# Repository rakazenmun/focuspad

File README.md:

# Focuspad

Focuspad is a six-key productivity macropad built around the Seeed Studio XIAO
RP2040. It combines a 2×3 diode matrix, a pressable rotary encoder, and a
128×32 OLED in a compact 3D-printed enclosure.

I wanted a small desktop controller that keeps the shortcuts I use most within
one hand. The default KMK layout provides Copy, Paste, Undo, Reopen Closed Tab,
Find, and Enter. Turning the encoder changes volume; pressing it mutes.

## PCB

The two-layer PCB is 97×68 mm. Six 1N4148 diodes prevent ghosting in the 2×3
matrix. The OLED uses D4/D5 for I²C, and the encoder uses D7–D9. All footprints
are embedded in the KiCad board file.

KiCad 10 error-level DRC result: **0 violations and 0 unconnected pads**.
KiCad 10 error-level ERC result: **0 violations**. Reports are included in the
`PCB` directory. The design has not yet been manufactured or hardware-tested.

## Case

The case is a two-part PLA print with a 1.5 mm MX switch plate, four M3 heat-set
bosses, a USB-C opening, and 0.25 mm clearance around the PCB. The complete
assembly is in `CAD/Focuspad_Assembly.step`; printable STEP and STL parts are in
`production/`.

## Firmware

`Firmware/main.py` is original KMK firmware for CircuitPython. Installation and
library requirements are documented in `Firmware/README.md`. A production copy
is available at `production/main.py`.

## Repository structure

- `CAD/` — complete STEP assembly
- `PCB/` — KiCad project, schematic, PCB, DRC, and ERC reports
- `Firmware/` — KMK source and installation notes
- `production/` — Gerbers, printable case parts, and firmware
- `assets/` — README renders
- `BOM.csv` — bill of materials with links

## Bill of materials

| Qty | Part |
|---:|---|
| 1 | Seeed Studio XIAO RP2040 |
| 6 | MX-compatible switches |
| 6 | 1U keycaps |
| 6 | 1N4148 DO-35 diodes |
| 1 | EC11 rotary encoder with push switch |
| 1 | 0.91-inch 128×32 SSD1306 OLED |
| 4 | M3×16 socket-head screws |
| 4 | M3×5×4 heat-set inserts |
| 1 | Two-layer PCB |
| 1 | Two-part PLA case |

See `BOM.csv` for source links and notes.

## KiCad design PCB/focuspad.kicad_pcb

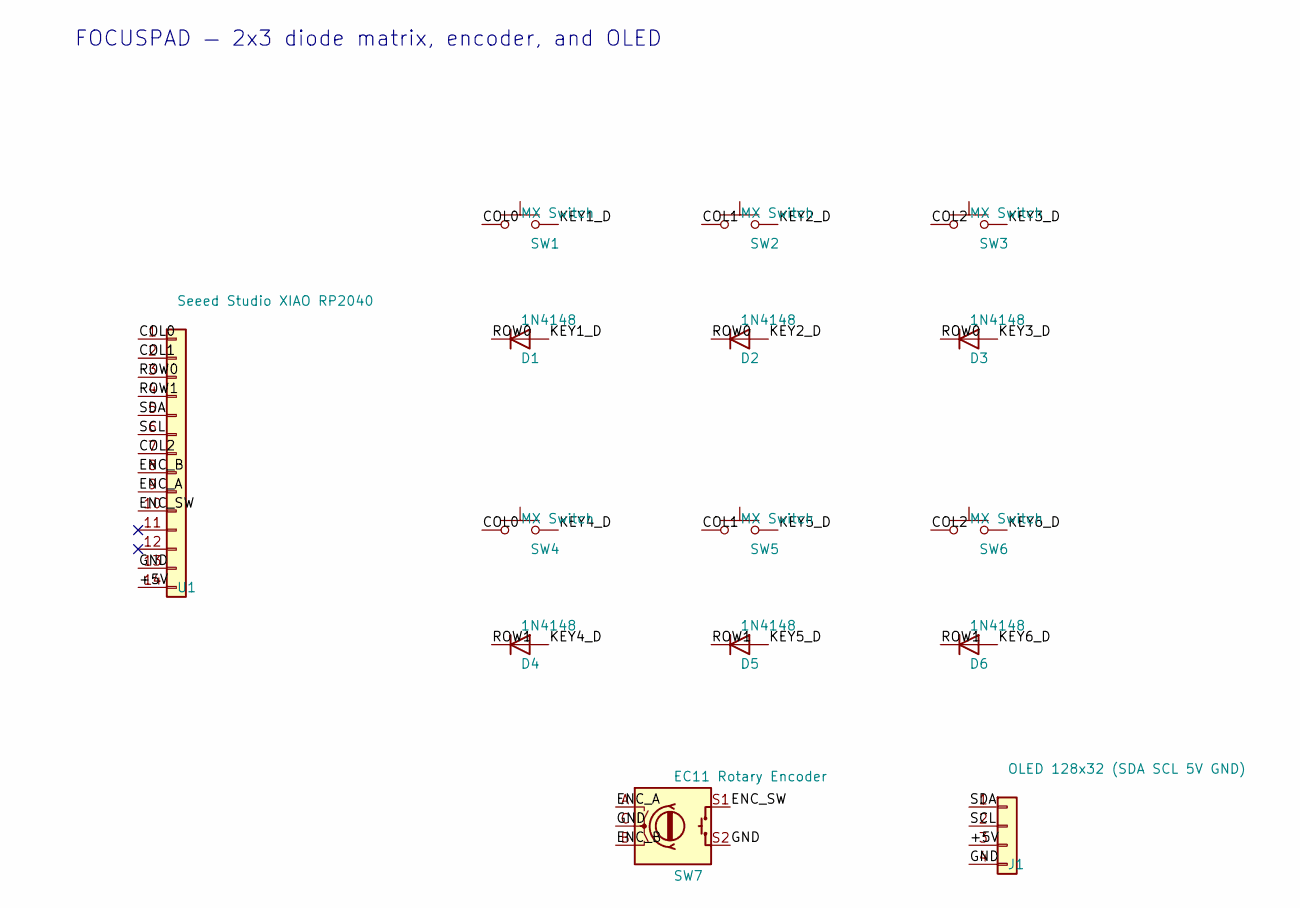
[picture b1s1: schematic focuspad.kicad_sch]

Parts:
D1, D2, D3, D4, D5, D6: 1N4148; D_DO-35_SOD27_P7.62mm_Horizontal
J1: OLED 128x32 (SDA SCL 5V GND); PinHeader_1x04_P2.54mm_Vertical
SW1, SW2, SW3, SW4, SW5, SW6: MX Switch; MX-Solderable-1U
SW7: EC11 Rotary Encoder; RotaryEncoder_Alps_EC11E-Switch_Vertical_H20mm
U1: Seeed Studio XIAO RP2040; XIAO-Generic-Hybrid-14P-2.54-21X17.8MM

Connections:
+5V: J1.3, U1.14 (5V)
COL0: SW1.1, SW4.1, U1.1 (PA02_A0_D0)
COL1: SW2.1, SW5.1, U1.2 (PA4_A1_D1)
COL2: SW3.1, SW6.1, U1.7 (PB08_A6_D6_TX)
ENC_A: SW7.A, U1.9 (PA7_A8_D8_SCK)
ENC_B: SW7.B, U1.8 (PB09_A7_D7_RX)
ENC_SW: SW7.S1, U1.10 (PA5_A9_D9_MISO)
GND: J1.4, SW7.C, SW7.S2, U1.13 (GND)
K1_D: D1.2 (A), SW1.2
K2_D: D2.2 (A), SW2.2
K3_D: D3.2 (A), SW3.2
K4_D: D4.2 (A), SW4.2
K5_D: D5.2 (A), SW5.2
K6_D: D6.2 (A), SW6.2
ROW0: D1.1 (K), D2.1 (K), D3.1 (K), U1.3 (PA10_A2_D2)
ROW1: D4.1 (K), D5.1 (K), D6.1 (K), U1.4 (PA11_A3_D3)
SCL: J1.2, U1.6 (PA9_A5_D5_SCL)
SDA: J1.1, U1.5 (PA8_A4_D4_SDA)

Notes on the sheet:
FOCUSPAD — 2x3 diode matrix, encoder, and OLED

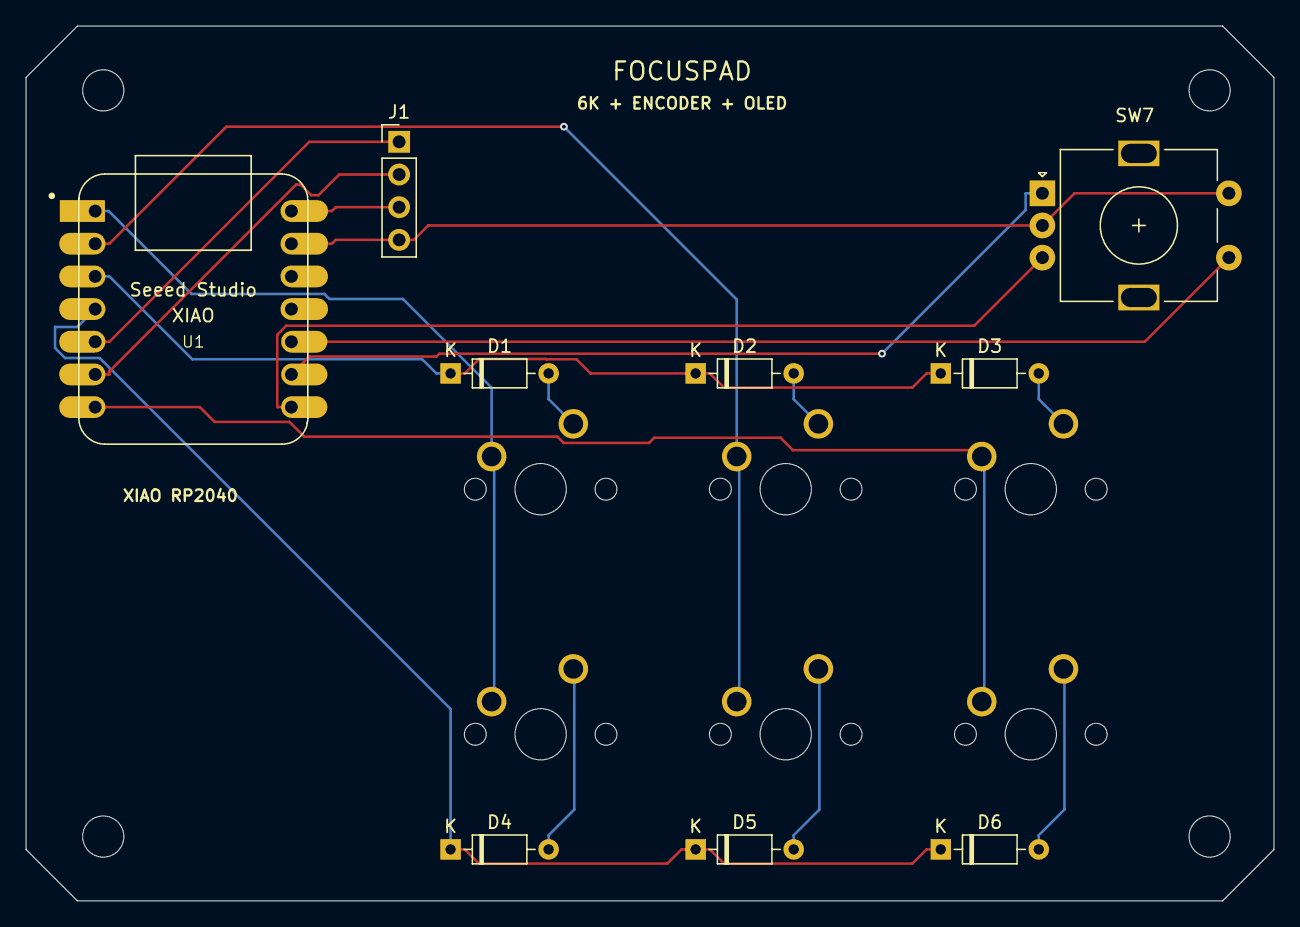
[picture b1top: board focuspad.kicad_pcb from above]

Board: 2 copper layers, 97.0 x 68.0 mm, 19 parts (0 on the bottom side), 18 nets.

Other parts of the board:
H1, H2, H3, H4: M3 Mounting Hole; MountingHole_3.2mm_M3
